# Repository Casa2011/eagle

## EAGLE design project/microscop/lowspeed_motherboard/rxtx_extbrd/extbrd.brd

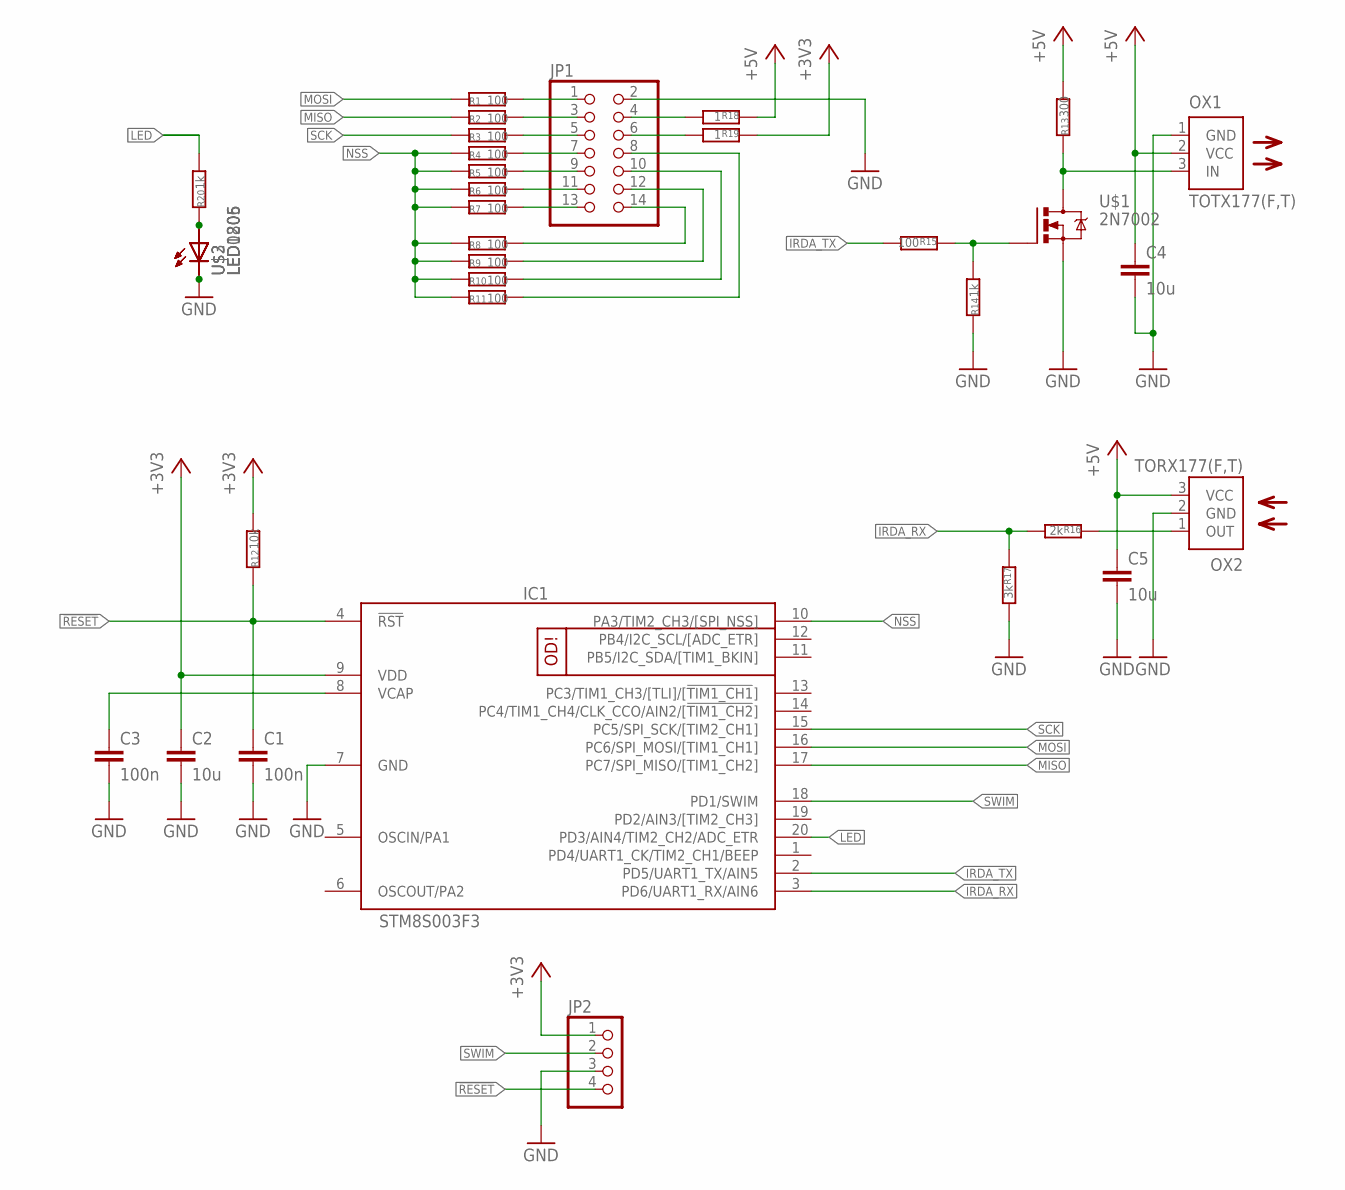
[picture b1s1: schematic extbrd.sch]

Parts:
C1, C3: 100n; C0603
C2, C4, C5: 10u; C0805
IC1: STM8S003F3; TSSOP20
JP1: PINHD-2X07_2.54-SMD; 2X07SMD
JP2: PINHD-1X04_2.54-SMD; 1X04SMD
OX1: TOTX177(F,T); TOTX
OX2: TORX177(F,T); TORX
R1, R2, R3, R4, R5, R6, R7, R8, R9, R10, R11, R15: 100; 0603
R12: 10k; 0603
R13: 300; 0603
R14, R20: 1k; 0603
R16: 2k; 0603
R17: 3k; 0603
R18, R19: 1; 0603
U$1: 2N7002; SOT23
U$2: LED0805; 0805-LED
U$3: LED1206; 1206-LED

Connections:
!RESET: C1.1, IC1.4 (!RST), JP2.4, R12.1
+3V3: C2.1, IC1.9 (VDD), JP2.1, R12.2, R19.1
+5V: C4.1, C5.1, OX1.2 (VCC), OX2.3 (VCC), R13.2, R18.1
GND: C1.2, C2.2, C3.2, C4.2, C5.2, IC1.7 (GND), JP1.2, JP2.3, OX1.1 (GND), OX2.2 (GND), R14.1, R17.2, U$1.2 (S), U$2.C, U$3.C
IRDA_RX: IC1.3 (PD6/UART1_RX/AIN6), R16.2, R17.1
IRDA_TX: IC1.2 (PD5/UART1_TX/AIN5), R15.2
LED: IC1.20 (PD3/AIN4/TIM2_CH2/ADC_ETR), R20.2
MISO: IC1.17 (PC7/SPI_MISO/[TIM1_CH2]), R2.1
MOSI: IC1.16 (PC6/SPI_MOSI/[TIM1_CH1]), R1.1
unnamed: JP1.5, R3.2
unnamed: JP1.3, R2.2
unnamed: JP1.1, R1.2
unnamed: JP1.4, R18.2
unnamed: JP1.7, R4.2
unnamed: JP1.9, R5.2
unnamed: JP1.11, R6.2
unnamed: JP1.13, R7.2
unnamed: JP1.14, R8.2
unnamed: JP1.12, R9.2
unnamed: JP1.10, R10.2
unnamed: JP1.8, R11.2
unnamed: C3.1, IC1.8 (VCAP)
unnamed: OX1.3 (IN), R13.1, U$1.3 (D)
unnamed: JP1.6, R19.2
unnamed: R14.2, R15.1, U$1.1 (G)
unnamed: R20.1, U$2.A, U$3.A
unnamed: OX2.1 (OUT), R16.1
NSS: IC1.10 (PA3/TIM2_CH3/[SPI_NSS]), R4.1, R5.1, R6.1, R7.1, R8.1, R9.1, R10.1, R11.1
SCK: IC1.15 (PC5/SPI_SCK/[TIM2_CH1]), R3.1
SWIM: IC1.18 (PD1/SWIM), JP2.2

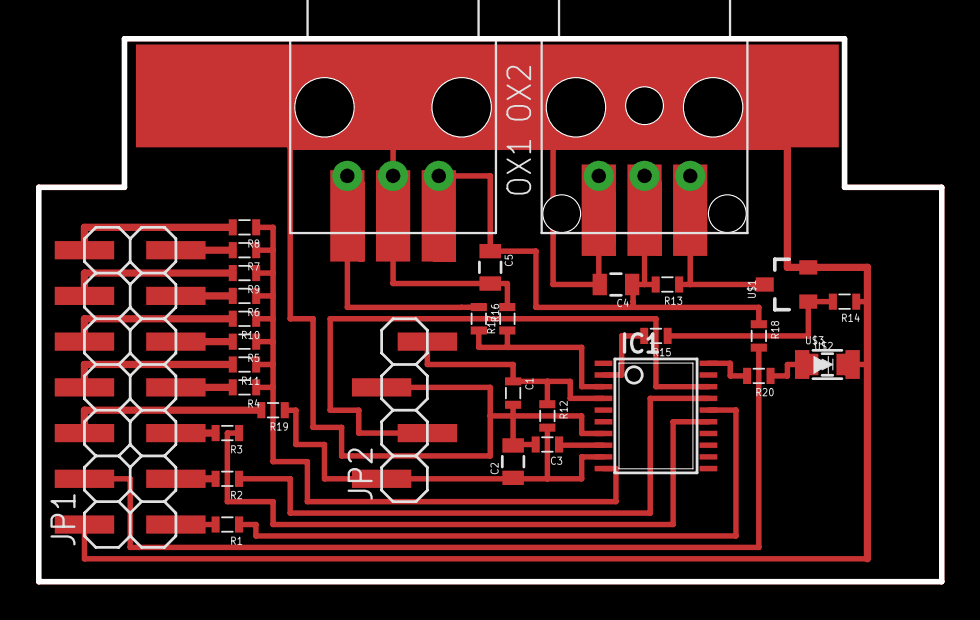
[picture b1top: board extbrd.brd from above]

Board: 2 copper layers, 50.2 x 30.2 mm, 33 parts (0 on the bottom side), 30 nets.

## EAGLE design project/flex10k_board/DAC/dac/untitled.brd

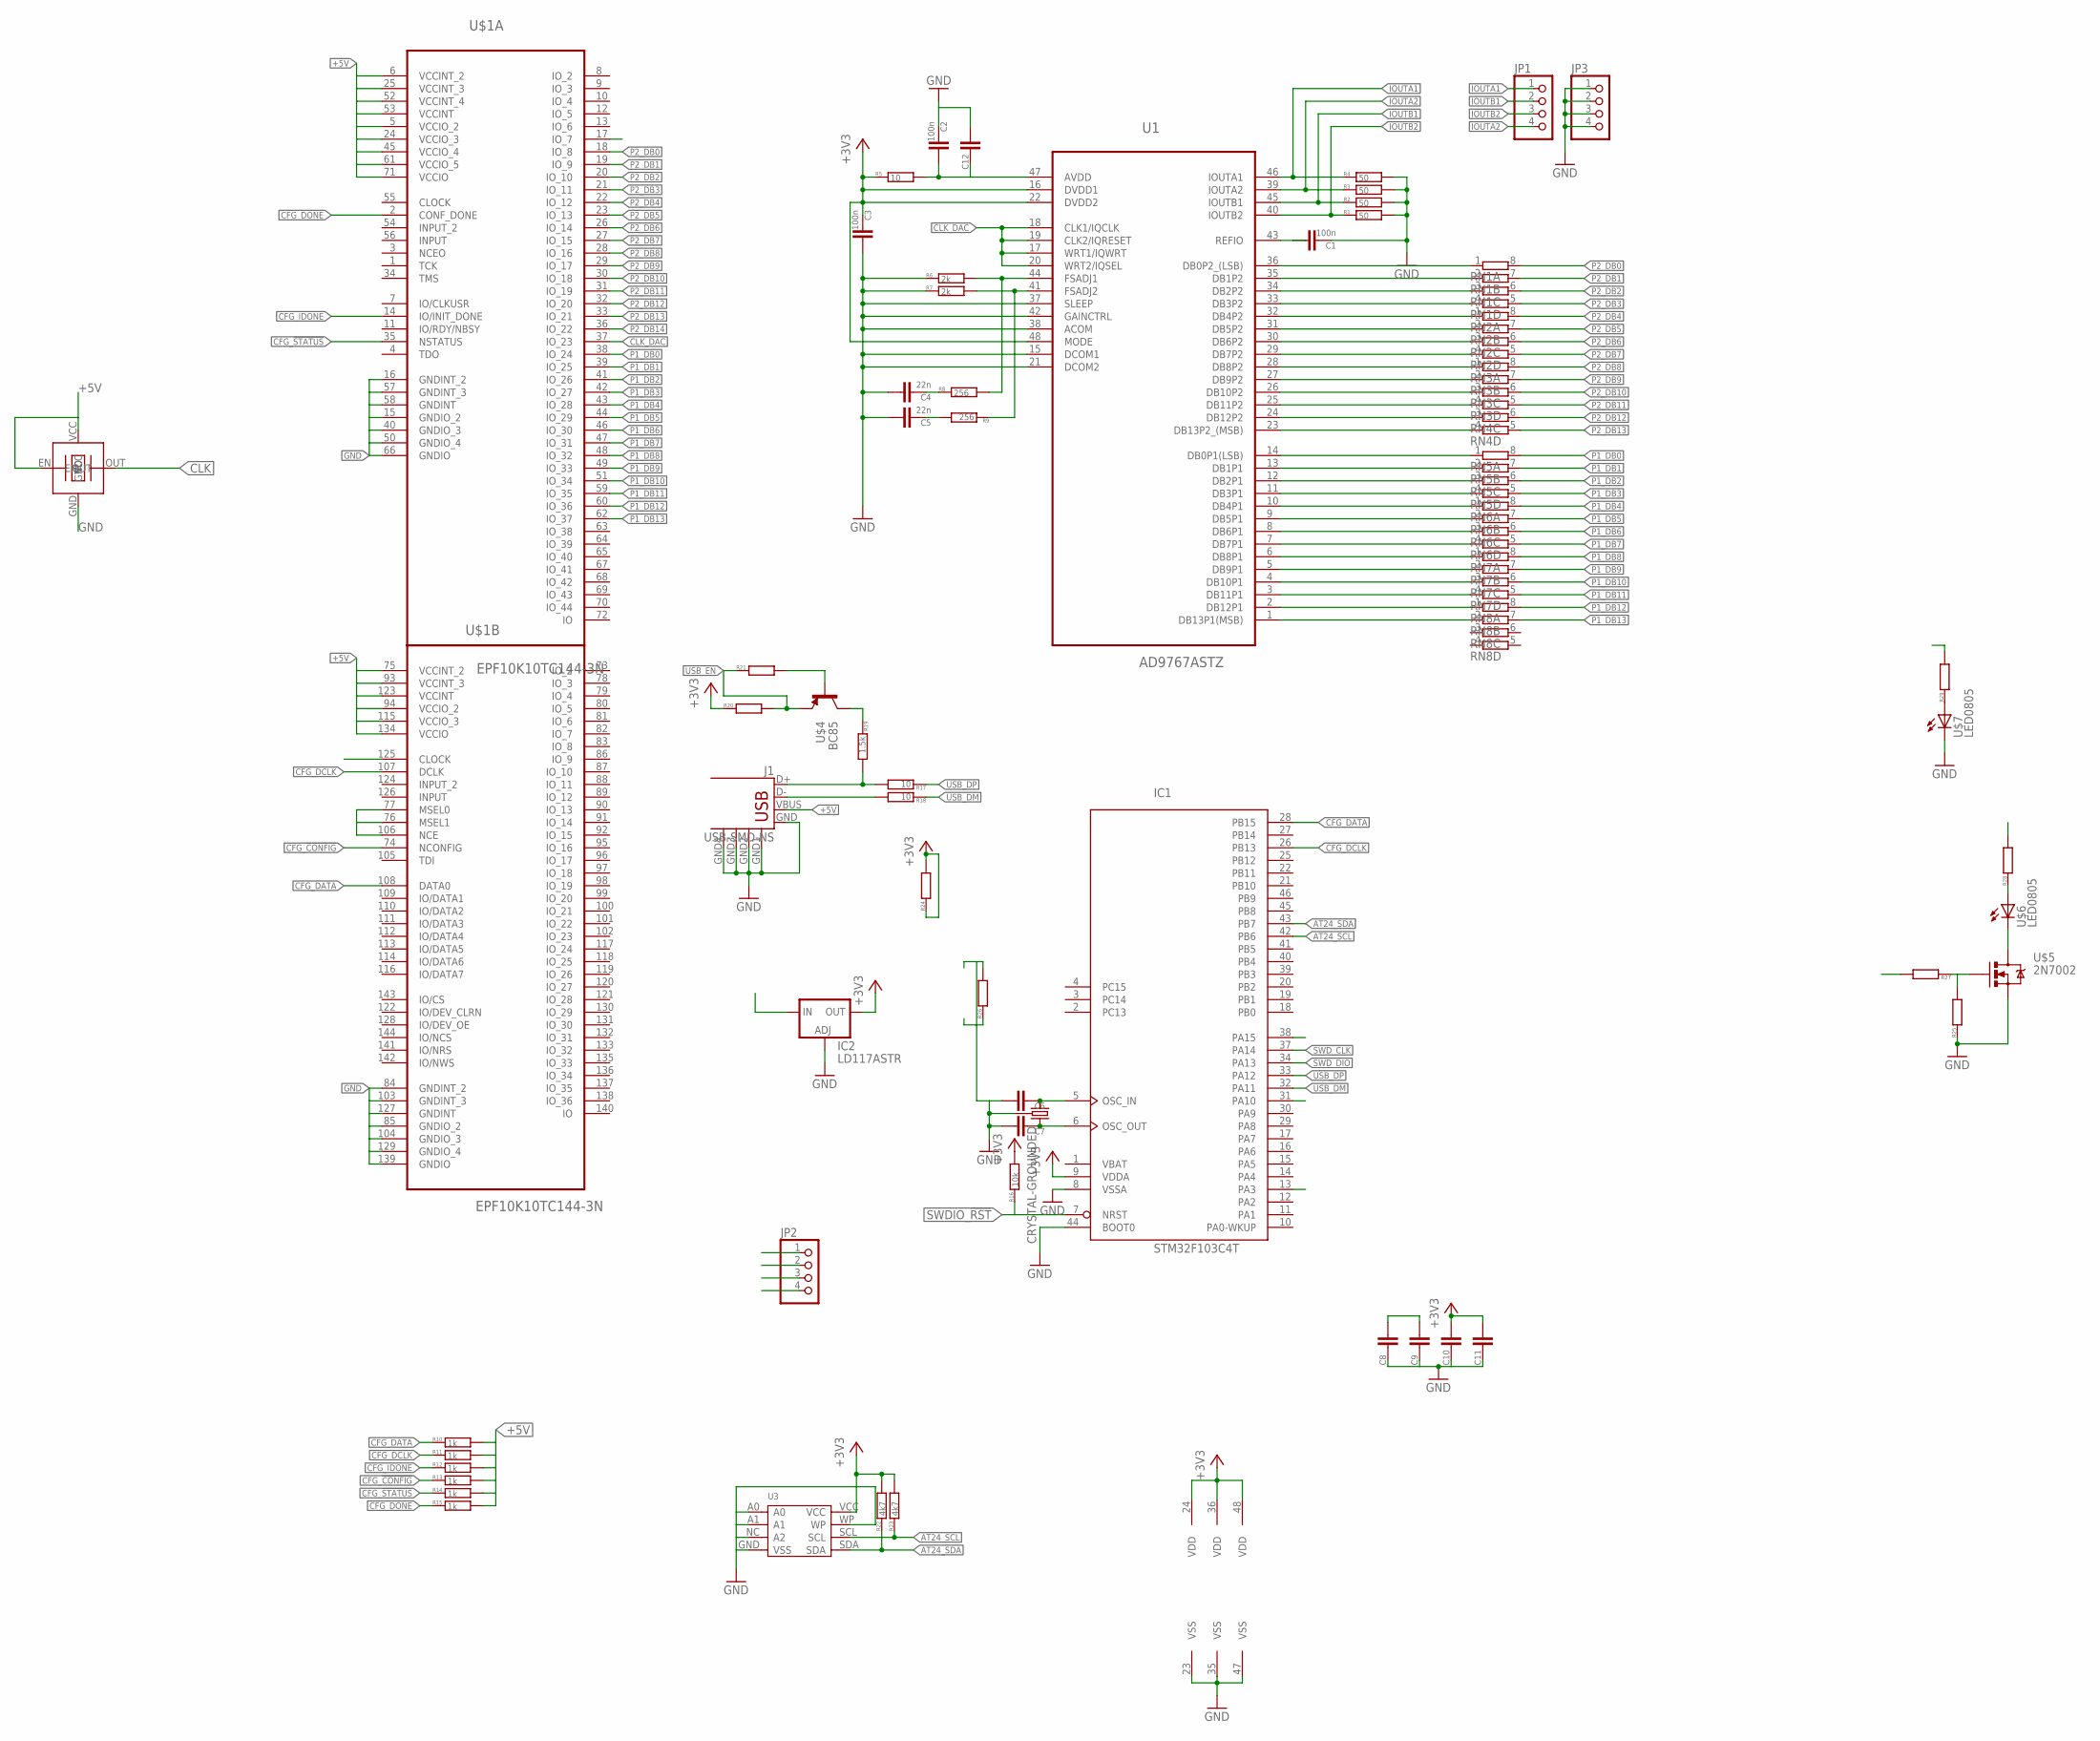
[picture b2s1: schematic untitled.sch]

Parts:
C1, C2, C3: 100n; C0805
C4, C5: 22n; C0805
C6, C7: CC0603; C0603
C8, C9, C10, C11, C12: CC0805; C0805
IC1: STM32F103C4T; LQFP48
IC2: LD117ASTR; SOT223
J1: USB-SMD-NS; USB-MINIB-NOSTOP
JP1, JP2, JP3: PINHD-1X04_2.54; 1X04
R1, R2, R3, R4: 50; R0805
R5: 10; R0805
R6, R7: 2k; R0805
R8, R9: 256; R0805
R10, R11, R12, R13, R14, R15: 1k; 0603
R16: 10k; 0603
R17, R18: 10; 0603
R19: 1.5k; 0603
R20, R21, R25, R26, R27, R28, R29: R0603; 0603
R22, R23: 4k7; 0603
R24: R1206
RN1, RN2, RN3, RN4, RN5, RN6, RN7, RN8: 4R-N0402ARV341; 4X0402ARV341
U1: AD9767ASTZ; QFP50P900X900X160-48N
U3: EEPROM-CAT24C256WI-GT3(SOIC8)QFN; QFN
U$1: EPF10K10TC144-3N; QFP50P2200X2200X160-144N
U$2: TXC-BA; 7X5
U$3: CRYSTAL-GROUNDED; CRYSTAL-SMD-5X3
U$4: BC85; SOT23
U$5: 2N7002; SOT23
U$6, U$7: LED0805; 0805-LED

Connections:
+3V3: C3.2, C10.1, C11.1, IC1.9 (VDDA), IC1.24 (VDD), IC1.36 (VDD), IC1.48 (VDD), IC2.4 (OUT), R5.1, R16.2, R20.1, R22.2, R23.2, R24.1, R24.2, U1.16 (DVDD1), U1.22 (DVDD2), U1.48 (MODE), U3.VCC
+5V: C8.1, C9.1, IC2.3 (IN), J1.VBUS, R10.2, R11.2, R12.2, R13.2, R14.2, R15.2, R28.2, U$1.5 (VCCIO_2), U$1.6 (VCCINT_2), U$1.24 (VCCIO_3), U$1.25 (VCCINT_3), U$1.45 (VCCIO_4), U$1.52 (VCCINT_4), U$1.53 (VCCINT), U$1.61 (VCCIO_5), U$1.71 (VCCIO), U$1.75 (VCCINT_2), U$1.93 (VCCINT_3), U$1.94 (VCCIO_2), U$1.115 (VCCIO_3), U$1.123 (VCCINT), U$1.134 (VCCIO), U$2.EN, U$2.VCC
AT24_SCL: IC1.42 (PB6), R23.1, U3.SCL
AT24_SDA: IC1.43 (PB7), R22.1, U3.SDA
CFG_!CONFIG: IC1.31 (PA10), R13.1, U$1.74 (NCONFIG)
CFG_!STATUS: R14.1, U$1.35 (NSTATUS)
CFG_DATA: IC1.28 (PB15), R10.1, U$1.108 (DATA0)
CFG_DCLK: IC1.26 (PB13), R11.1, U$1.107 (DCLK)
CFG_DONE: R15.1, R27.2, U$1.2 (CONF_DONE)
CFG_IDONE: R12.1, U$1.14 (IO/INIT_DONE)
CLK: U$1.125 (CLOCK), U$2.OUT
CLK_DAC: U1.17 (WRT1/IQWRT), U1.18 (CLK1/IQCLK), U1.19 (CLK2/IQRESET), U1.20 (WRT2/IQSEL), U$1.37 (IO_23)
FSADJ1: R6.2, R8.2, U1.44 (FSADJ1)
FSADJ2: R7.2, R9.1, U1.41 (FSADJ2)
GND: C1.2, C2.2, C3.1, C4.1, C5.1, C6.1, C7.1, C8.2, C9.2, C10.2, C11.2, C12.1, IC1.8 (VSSA), IC1.23 (VSS), IC1.35 (VSS), IC1.38 (PA15), IC1.44 (BOOT0), IC1.47 (VSS), IC2.1 (ADJ), J1.GND, J1.GND1 (GND), J1.GND2 (GND), J1.GND3 (GND), J1.GND4 (GND), JP2.1, JP3.1, JP3.2, JP3.3, JP3.4, R1.2, R2.2, R3.2, R4.2, R6.1, R7.1, R25.1, R26.1, R26.2, U1.15 (DCOM1), U1.21 (DCOM2), U1.37 (SLEEP), U1.38 (ACOM), U1.42 (GAINCTRL), U3.A0, U3.A1, U3.GND (VSS), U3.NC (A2), U3.WP, U$1.15 (GNDIO_2), U$1.16 (GNDINT_2), U$1.40 (GNDIO_3), U$1.50 (GNDIO_4), U$1.57 (GNDINT_3), U$1.58 (GNDINT), U$1.66 (GNDIO), U$1.76 (MSEL1), U$1.77 (MSEL0), U$1.84 (GNDINT_2), U$1.85 (GNDIO_2), U$1.103 (GNDINT_3), U$1.104 (GNDIO_3), U$1.106 (NCE), U$1.127 (GNDINT), U$1.129 (GNDIO_4), U$1.139 (GNDIO), U$2.GND, U$3.2 (3), U$3.4 (3), U$5.2 (S), U$7.C
IO7: R29.2, U$1.17 (IO_7)
IOUTA1: JP1.1, R4.1, U1.46 (IOUTA1)
IOUTA2: JP1.4, R3.1, U1.39 (IOUTA2)
IOUTB1: JP1.2, R2.1, U1.45 (IOUTB1)
IOUTB2: JP1.3, R1.1, U1.40 (IOUTB2)
unnamed: C4.2, R8.1
unnamed: C5.2, R9.2
unnamed: C2.1, C12.2, R5.2, U1.47 (AVDD)
unnamed: C1.1, U1.43 (REFIO)
unnamed: J1.D-, R18.2
unnamed: R25.2, R27.1, U$5.1 (G)
unnamed: J1.D+, R17.2, R19.2
unnamed: R19.1, U$4.3 (C)
unnamed: C6.2, IC1.5 (OSC_IN), U$3.3 (1)
unnamed: C7.2, IC1.6 (OSC_OUT), U$3.1 (2)
unnamed: R21.2, U$4.1 (B)
unnamed: R29.1, U$7.A
unnamed: U$5.3 (D), U$6.C
unnamed: R28.1, U$6.A
P1_DB0: RN5.8 (2), U$1.38 (IO_24)
P1_DB0=: RN5.1, U1.14 (DB0P1(LSB))
P1_DB1: RN5.7 (2), U$1.39 (IO_25)
P1_DB1=: RN5.2 (1), U1.13 (DB1P1)
P1_DB2: RN5.6 (2), U$1.41 (IO_26)
P1_DB2=: RN5.3 (1), U1.12 (DB2P1)
P1_DB3: RN5.5 (2), U$1.42 (IO_27)
P1_DB3=: RN5.4 (1), U1.11 (DB3P1)
P1_DB4: RN6.8 (2), U$1.43 (IO_28)
P1_DB4=: RN6.1, U1.10 (DB4P1)
P1_DB5: RN6.7 (2), U$1.44 (IO_29)
P1_DB5=: RN6.2 (1), U1.9 (DB5P1)
P1_DB6: RN6.6 (2), U$1.46 (IO_30)
P1_DB6=: RN6.3 (1), U1.8 (DB6P1)
P1_DB7: RN6.5 (2), U$1.47 (IO_31)
P1_DB7=: RN6.4 (1), U1.7 (DB7P1)
P1_DB8: RN7.8 (2), U$1.48 (IO_32)
P1_DB8=: RN7.1, U1.6 (DB8P1)
P1_DB9: RN7.7 (2), U$1.49 (IO_33)
P1_DB9=: RN7.2 (1), U1.5 (DB9P1)
P1_DB10: RN7.6 (2), U$1.51 (IO_34)
P1_DB10=: RN7.3 (1), U1.4 (DB10P1)
P1_DB11: RN7.5 (2), U$1.59 (IO_35)
P1_DB11=: RN7.4 (1), U1.3 (DB11P1)
P1_DB12: RN8.8 (2), U$1.60 (IO_36)
P1_DB12=: RN8.1, U1.2 (DB12P1)
P1_DB13: RN8.7 (2), U$1.62 (IO_37)
P1_DB13=: RN8.2 (1), U1.1 (DB13P1(MSB))
P2_DB0: RN1.8 (2), U$1.18 (IO_8)
P2_DB0=: RN1.1, U1.36 (DB0P2_(LSB))
P2_DB1: RN1.7 (2), U$1.19 (IO_9)
P2_DB1=: RN1.2 (1), U1.35 (DB1P2)
P2_DB2: RN1.6 (2), U$1.20 (IO_10)
P2_DB2=: RN1.3 (1), U1.34 (DB2P2)
P2_DB3: RN1.5 (2), U$1.21 (IO_11)
P2_DB3=: RN1.4 (1), U1.33 (DB3P2)
P2_DB4: RN2.8 (2), U$1.22 (IO_12)
P2_DB4=: RN2.1, U1.32 (DB4P2)
P2_DB5: RN2.7 (2), U$1.23 (IO_13)
P2_DB5=: RN2.2 (1), U1.31 (DB5P2)
P2_DB6: RN2.6 (2), U$1.26 (IO_14)
P2_DB6=: RN2.3 (1), U1.30 (DB6P2)
P2_DB7: RN2.5 (2), U$1.27 (IO_15)
P2_DB7=: RN2.4 (1), U1.29 (DB7P2)
P2_DB8: RN3.8 (2), U$1.28 (IO_16)
P2_DB8=: RN3.1, U1.28 (DB8P2)
P2_DB9: RN3.7 (2), U$1.29 (IO_17)
P2_DB9=: RN3.2 (1), U1.27 (DB9P2)
P2_DB10: RN3.6 (2), U$1.30 (IO_18)
P2_DB10=: RN3.3 (1), U1.26 (DB10P2)
P2_DB11: RN3.5 (2), U$1.31 (IO_19)
P2_DB11=: RN3.4 (1), U1.25 (DB11P2)
P2_DB12: RN4.6 (2), U$1.32 (IO_20)
P2_DB12=: RN4.3 (1), U1.24 (DB12P2)
P2_DB13: RN4.5 (2), U$1.33 (IO_21)
P2_DB13=: RN4.4 (1), U1.23 (DB13P2_(MSB))
P2_DB14: U$1.36 (IO_22)
SWDIO_!RST: IC1.7 (NRST), JP2.4, R16.1
SWD_CLK: IC1.37 (PA14), JP2.3
SWD_DIO: IC1.34 (PA13), JP2.2
USB_DM: IC1.32 (PA11), R18.1
USB_DP: IC1.33 (PA12), R17.1
USB_EN: IC1.13 (PA3), R20.2, R21.1, U$4.2 (E)
VBAT: IC1.1 (VBAT)

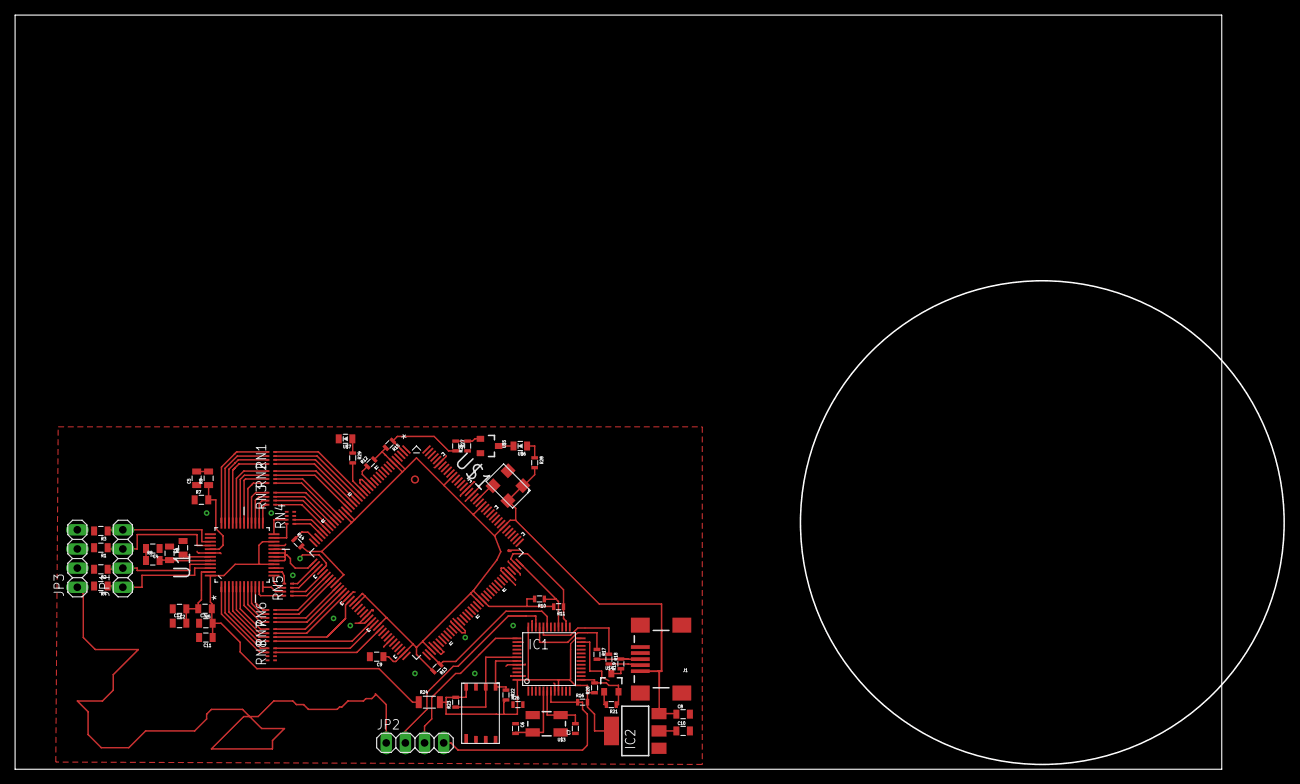
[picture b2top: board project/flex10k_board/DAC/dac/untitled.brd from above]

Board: 2 copper layers, 168.3 x 100.0 mm, 64 parts (0 on the bottom side), 96 nets.

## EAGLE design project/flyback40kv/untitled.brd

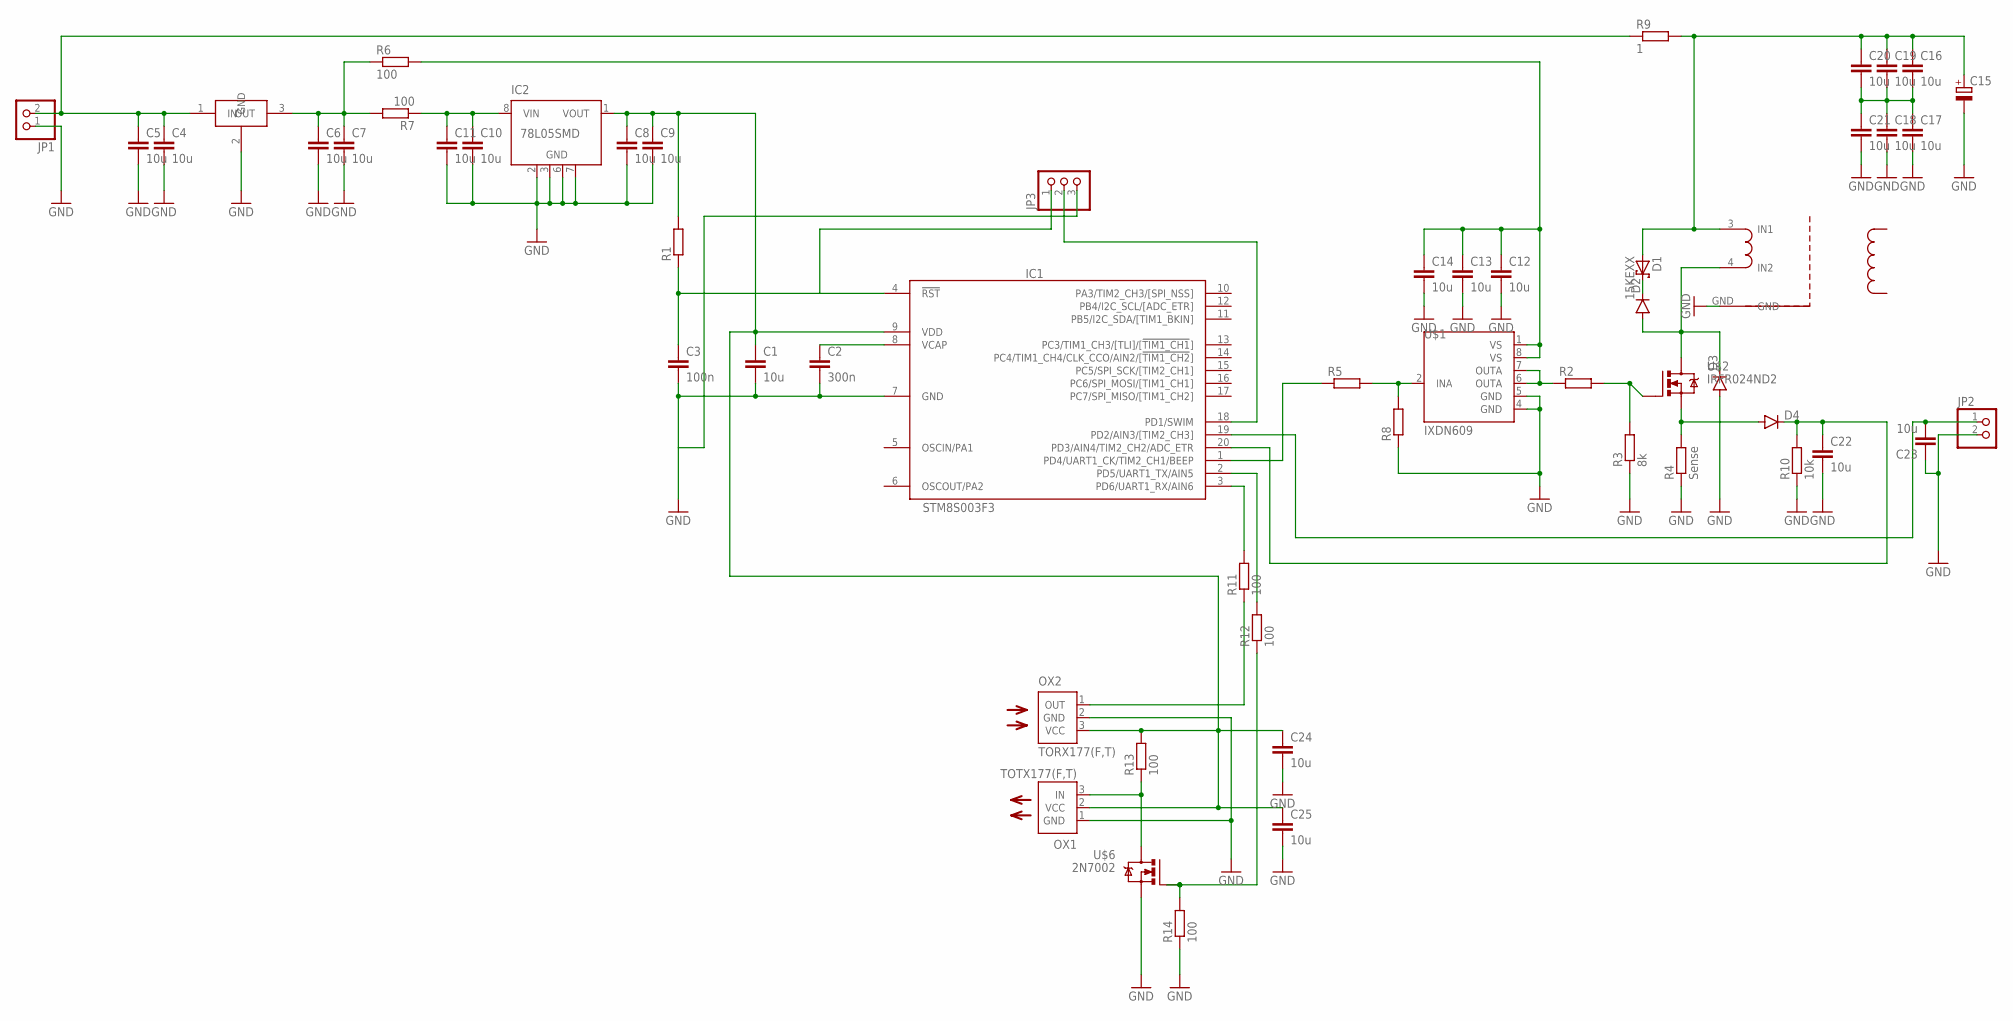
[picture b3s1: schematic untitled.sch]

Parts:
C1, C4, C5, C6, C7, C8, C9, C10, C11, C12, C13, C14, C16, C17, C18, C19, C20, C21, C22, C23, C24, C25: 10u; C0805
C2: 300n; C0805
C3: 100n; C0805
C15: CPOL-EUE7.5-16; E7,5-16
D1: 15KEXX; CB429-17
D2, D3: DIODESMA; SMA-DIODE
D4: DIODESOD123; SOD-123
IC1: STM8S003F3; TSSOP20
IC2: 78L05SMD; SO08
JP1, JP2: PINHD-1X2; 1X02
JP3: PINHD-1X3; 1X03
OX1: TOTX177(F,T); TOTX
OX2: TORX177(F,T); TORX
R1: R0603; 0603
R2, R5, R8: R0805
R3: 8k; R0805
R4: Sense; R2512
R6, R7: 100; R0805
R9: 1; R1206
R10: 10k; R0805
R11, R12, R13, R14: 100; 0603
U$1: IXDN609; SO08
U$2: IRFR024ND2; D2PACK
U$3: TVS-90P6
U$4: L7805C2T; D2PACK
U$6: 2N7002; SOT23

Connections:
GND: C1.2, C2.2, C3.2, C4.2, C5.2, C6.2, C7.2, C8.2, C9.2, C10.2, C11.2, C12.2, C13.2, C14.2, C15.-, C17.2, C18.2, C21.2, C22.2, C23.1, C24.2, C25.2, D3.A, IC1.7 (GND), IC2.2 (GND), IC2.3 (GND), IC2.6 (GND), IC2.7 (GND), JP1.1, JP2.2, JP3.3, OX1.1 (GND), OX2.2 (GND), R3.1, R4.1, R8.1, R10.1, R14.1, U$1.4 (GND), U$1.5 (GND), U$3.GND, U$4.2 (GND), U$6.2 (S)
unnamed: C3.1, IC1.4 (!RST), JP3.1, R1.1
unnamed: C12.1, C13.1, C14.1, R6.2, U$1.1 (VS), U$1.8 (VS)
unnamed: C2.1, IC1.8 (VCAP)
unnamed: C15.+, C16.1, C19.1, C20.1, D1.A, R9.2, U$3.3 (IN1)
unnamed: D1.C, D2.C
unnamed: R5.2, R8.2, U$1.2 (INA)
unnamed: R2.1, U$1.6 (OUTA), U$1.7 (OUTA)
unnamed: R2.2, R3.2, U$2.1 (G)
unnamed: D2.A, D3.C, U$2.2 (D), U$3.4 (IN2)
unnamed: C4.1, C5.1, JP1.2, R9.1, U$4.1 (IN)
unnamed: D4.A, R4.2, U$2.3 (S)
unnamed: C22.1, D4.C, IC1.20 (PD3/AIN4/TIM2_CH2/ADC_ETR), R10.2
unnamed: C23.2, IC1.19 (PD2/AIN3/[TIM2_CH3]), JP2.1
unnamed: IC1.1 (PD4/UART1_CK/TIM2_CH1/BEEP), R5.1
unnamed: IC1.3 (PD6/UART1_RX/AIN6), R11.2
unnamed: C16.2, C17.1, C18.1, C19.2, C20.2, C21.1
unnamed: R12.1, R14.2, U$6.1 (G)
unnamed: C1.1, C8.1, C9.1, C24.1, C25.1, IC1.9 (VDD), IC2.1 (VOUT), OX1.2 (VCC), OX2.3 (VCC), R1.2, R13.2
unnamed: C10.1, C11.1, IC2.8 (VIN), R7.1
unnamed: OX2.1 (OUT), R11.1
unnamed: C6.1, C7.1, R6.1, R7.2, U$4.3 (OUT)
unnamed: OX1.3 (IN), R13.1, U$6.3 (D)
unnamed: IC1.2 (PD5/UART1_TX/AIN5), R12.2
unnamed: IC1.18 (PD1/SWIM), JP3.2

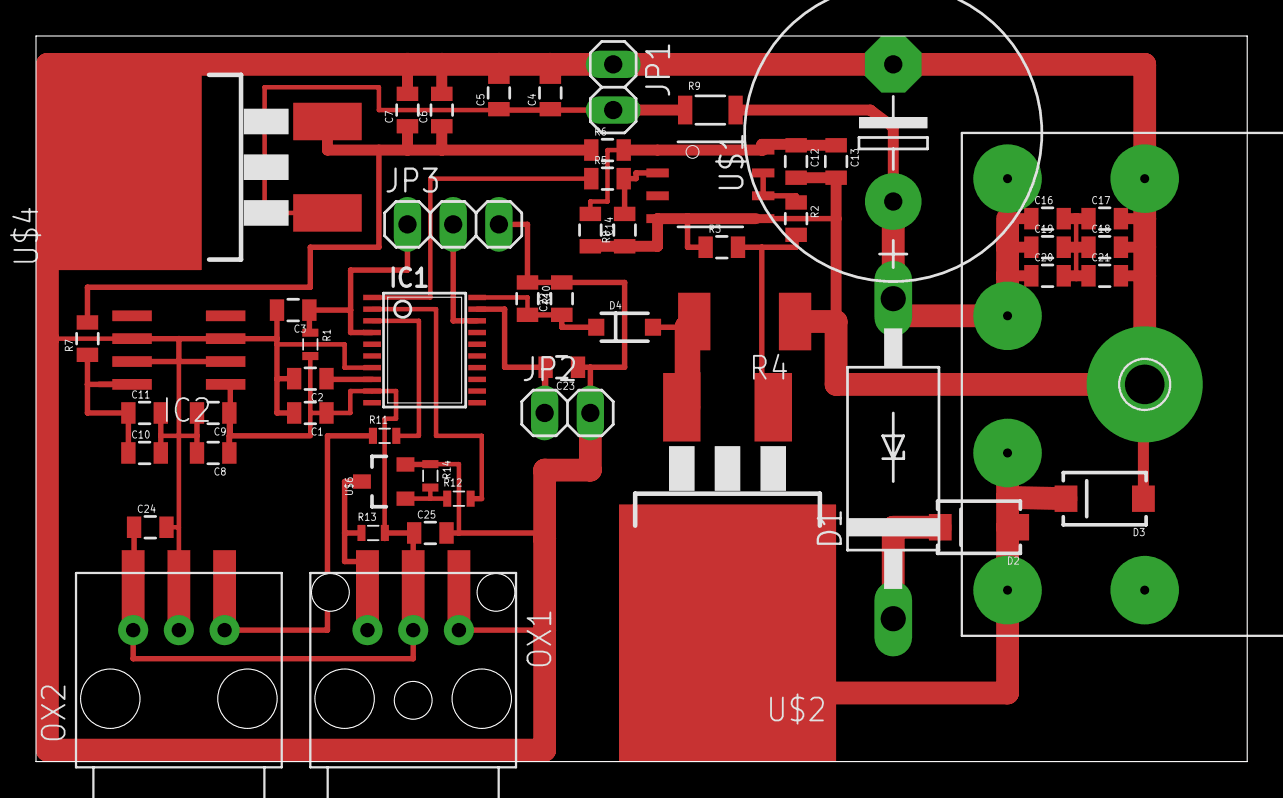
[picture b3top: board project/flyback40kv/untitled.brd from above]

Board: 2 copper layers, 67.3 x 40.3 mm, 55 parts (0 on the bottom side), 25 nets.

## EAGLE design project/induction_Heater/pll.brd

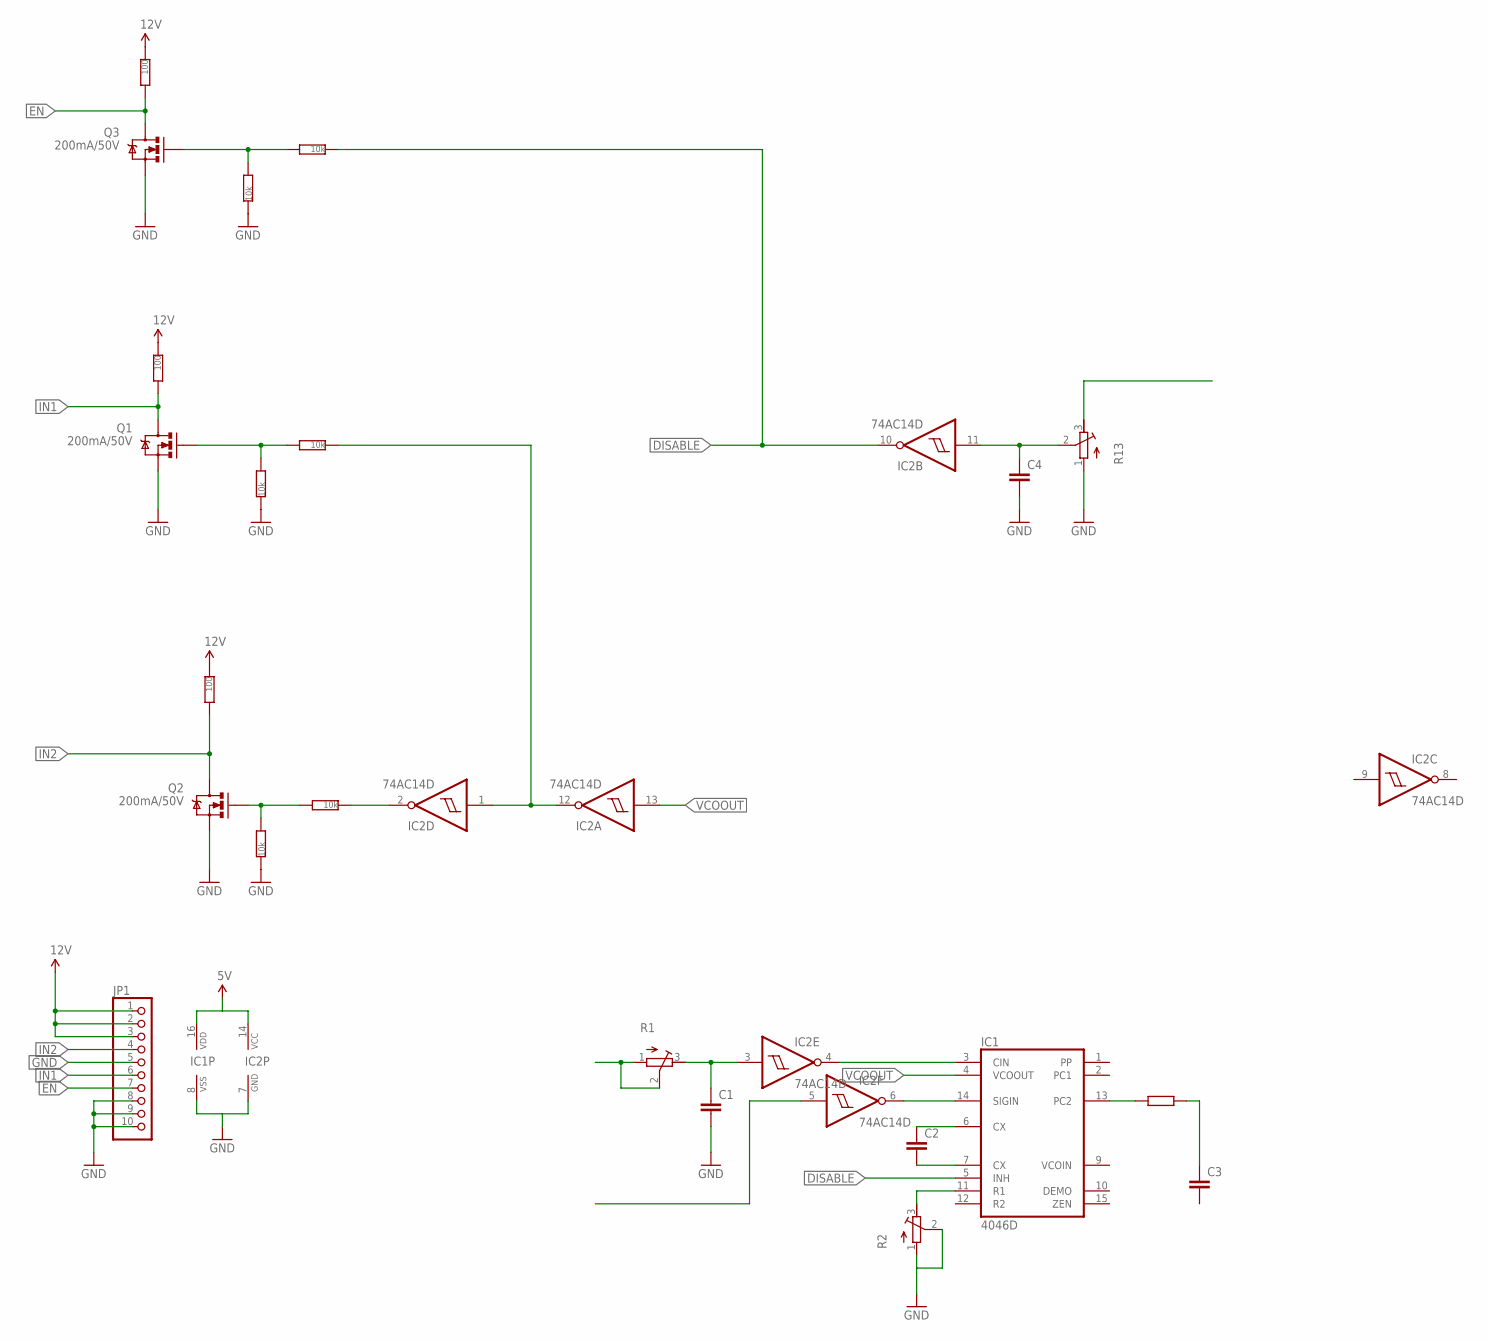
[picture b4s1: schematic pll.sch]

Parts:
C1, C2, C3, C4: CC0805; C0805
IC1: 4046D; SO16
IC2: 74AC14D; SO14
JP1: PINHD-1X10; 1X10
Q1, Q2, Q3: 200mA/50V; SOT23-3
R1, R2, R13: R-TRIMM64X; RTRIM64X
R3: R0805
R4, R5, R8: 100; R0805
R6, R7, R9, R11, R12: 10k; 0603
R10: 10k; R0805

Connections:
5V: IC1.16 (VDD), IC2.14 (VCC)
12V: JP1.1, JP1.2, JP1.3, R4.1, R5.1, R8.1
DISABLE: IC1.5 (INH), IC2.10 (O), R12.1
EN: JP1.7, Q3.3 (D), R8.2
GND: C1.2, C4.2, IC1.8 (VSS), IC2.7 (GND), JP1.5, JP1.8, JP1.9, JP1.10, Q1.2 (S), Q2.2 (S), Q3.2 (S), R2.1 (A), R2.2 (S), R6.1, R7.1, R9.1, R13.1 (A)
IN1: JP1.6, Q1.3 (D), R4.2
IN2: JP1.4, Q2.3 (D), R5.2
unnamed: IC1.14 (SIGIN), IC2.6 (O)
unnamed: IC1.3 (CIN), IC2.4 (O)
unnamed: C1.1, IC2.3 (I), R1.3 (E)
unnamed: R1.1 (A), R1.2 (S)
unnamed: C2.1, IC1.6 (CX)
unnamed: C2.2, IC1.7 (CX)
unnamed: Q3.1 (G), R9.2, R12.2
unnamed: IC2.1 (I), IC2.12 (O), R11.1
unnamed: Q2.1 (G), R7.2, R10.2
unnamed: IC1.13 (PC2), R3.2
unnamed: C3.1, R3.1
unnamed: Q1.1 (G), R6.2, R11.2
unnamed: IC2.2 (O), R10.1
unnamed: IC1.11 (R1), R2.3 (E)
unnamed: C4.1, IC2.11 (I), R13.2 (S)
VCOOUT: IC1.4 (VCOOUT), IC2.13 (I)

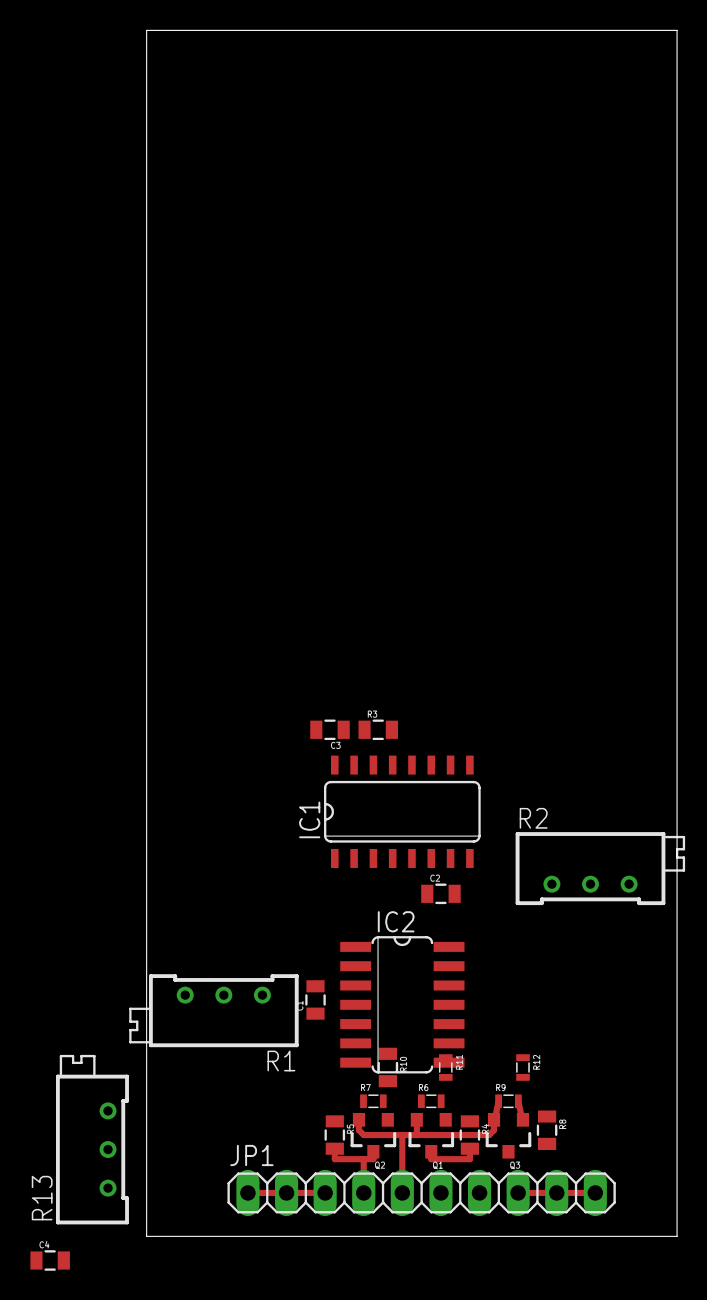
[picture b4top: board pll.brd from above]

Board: 2 copper layers, 34.9 x 79.4 mm, 23 parts (0 on the bottom side), 23 nets.

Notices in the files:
parts and their libraries:
SparkFun-Connectors: Licensing: Creative Commons ShareAlike 4.0 International - https://creativecommons.org/licenses/by-sa/4.0
SparkFun-Passives: Licensing: CC v3.0 Share-Alike You are welcome to use this library for commercial purposes.
